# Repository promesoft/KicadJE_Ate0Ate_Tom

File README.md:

# KicadJE_Ate0Ate_Tom
Based on Hexinverter

First Drum module

# Purpose
1 - Match Hexinverter sch with Resynthesis panel

# Status - delivered
## Initial 
| Stage  | Detail | Status |
| ------------- | ------------- | ------------- |
| create material  | sch/pcb | OK  |
| | gerber | OK |
| production  |   | ok |
|  | produced | ok |
|  | delivered | ok |

## Preliminary validation
| Test  | Detail | Status |
| ------------- | ------------- | ------------- |
| Initial Inspection | |  |
| Initial Technical Test |  | |
| Initial Product Test |  | |

## Secondary validation
| Test  | Detail | Status |
| ------------- | ------------- |------------- |
| Product Test |  | |
| Product Test |  |  |
| Quality | | |
| Quality |  |  |
| Long Term Product Test |  |  |
| Power Draw |  | 

## Errata
### Errata - Ate0Ate Tom

## Issues and Notes
### Tom
1 -

2 - 

# Pictures

# Inspiration from 
https://www.resynthesis.shop/epages/zuunneamm4zd.sf/en_GB/?ObjectPath=/Shops/zuunneamm4zd/Products/REEU-HEX-808-TM1

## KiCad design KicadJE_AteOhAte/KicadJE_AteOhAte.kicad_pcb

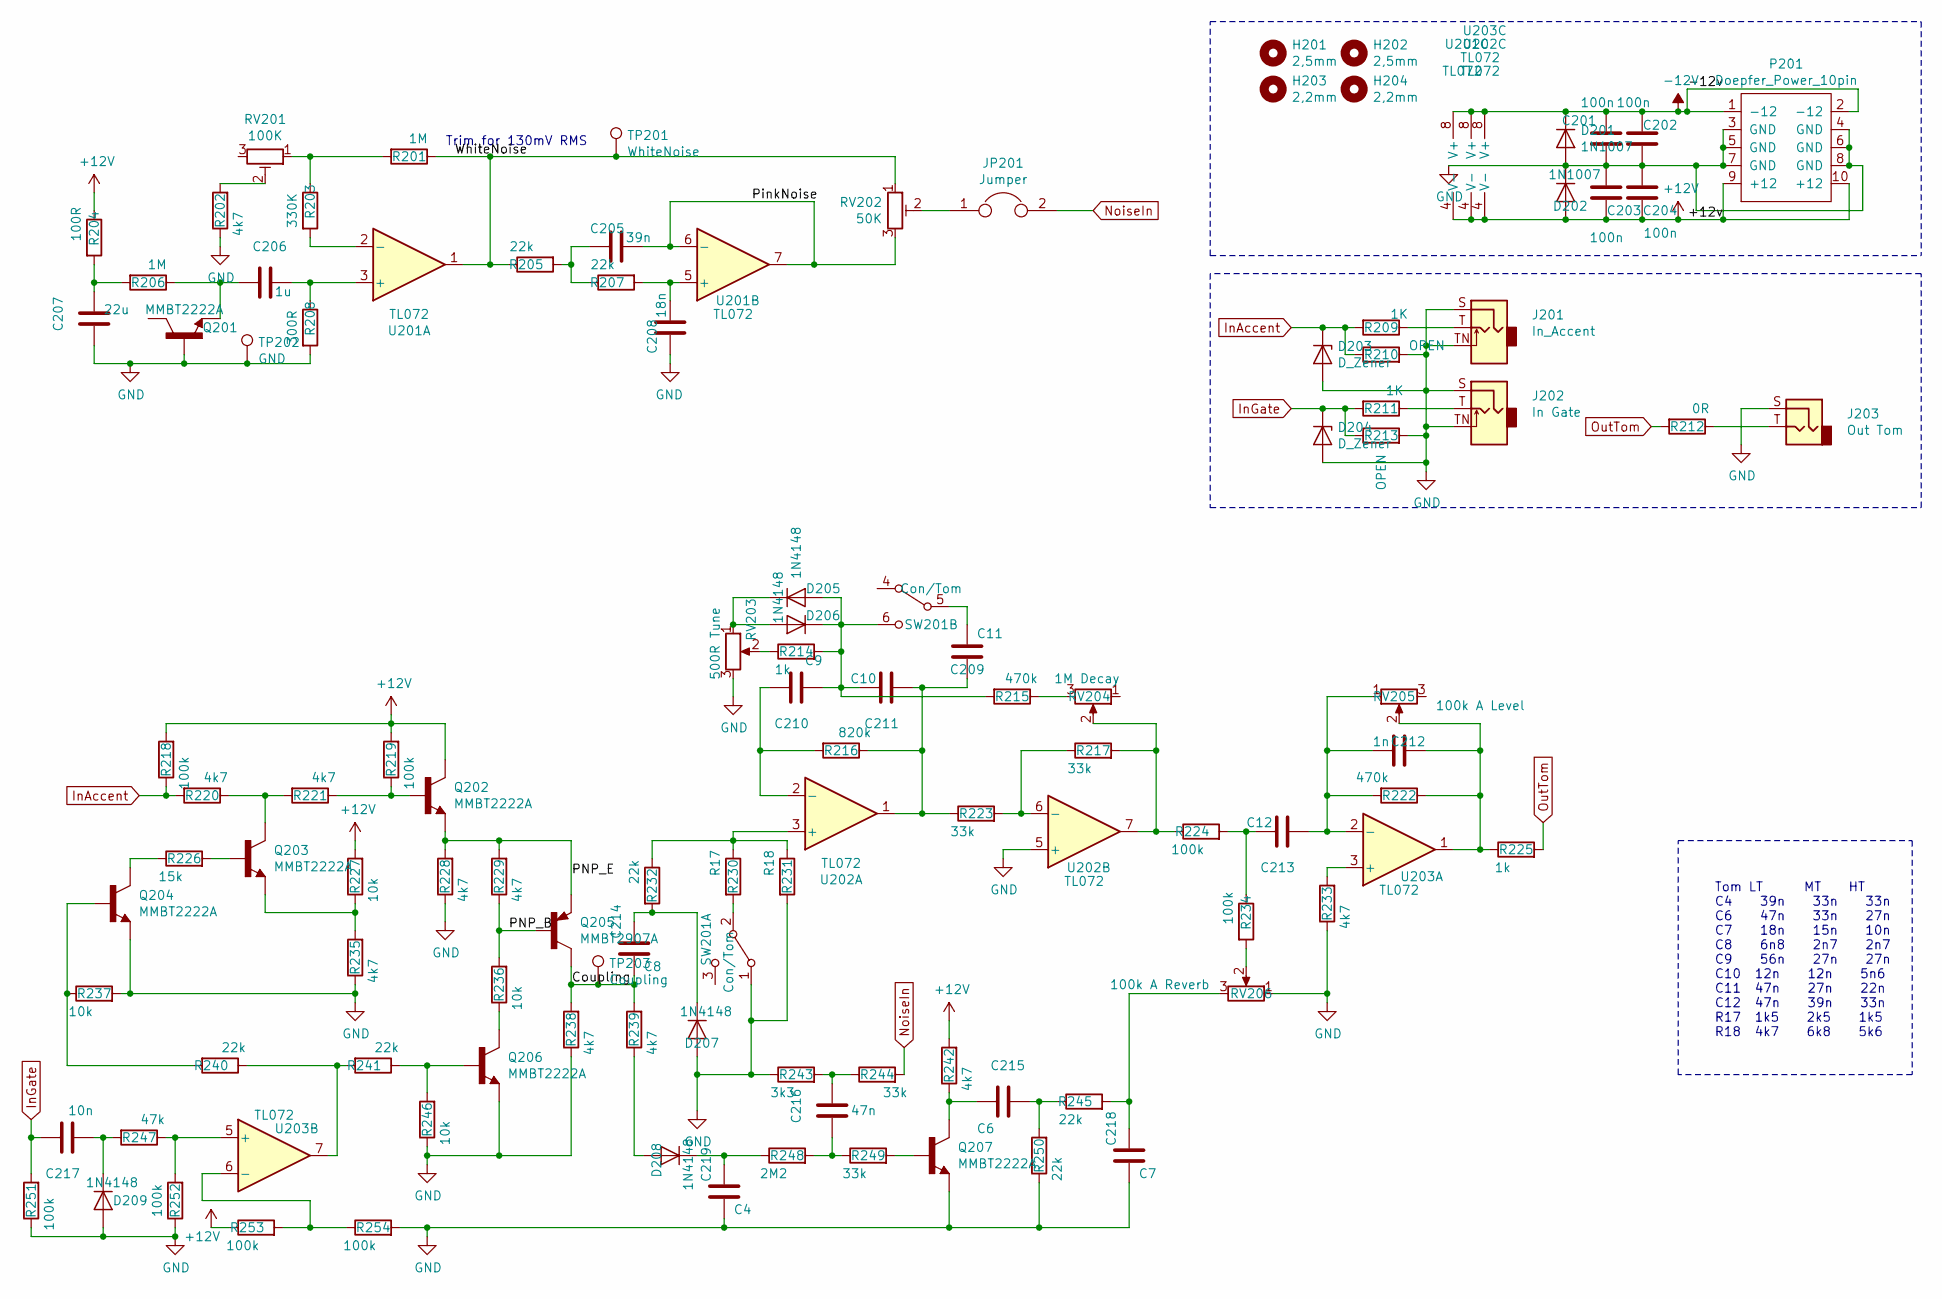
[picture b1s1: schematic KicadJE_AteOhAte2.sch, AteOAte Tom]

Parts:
C201, C202, C203, C204: 100n; C_0805_2012Metric_Pad1.15x1.40mm_HandSolder
C205: 39n; C_0805_2012Metric_Pad1.15x1.40mm_HandSolder
C206: 1u; C_0805_2012Metric_Pad1.15x1.40mm_HandSolder
C207: 22u; C_0805_2012Metric_Pad1.15x1.40mm_HandSolder
C208: 18n; C_0805_2012Metric_Pad1.15x1.40mm_HandSolder
C209: C11; C_0805_2012Metric_Pad1.15x1.40mm_HandSolder
C210: C9; C_0805_2012Metric_Pad1.15x1.40mm_HandSolder
C211: C10; C_0805_2012Metric_Pad1.15x1.40mm_HandSolder
C212: 1n; C_0805_2012Metric_Pad1.15x1.40mm_HandSolder
C213: C12; C_0805_2012Metric_Pad1.15x1.40mm_HandSolder
C214: C8; C_0805_2012Metric_Pad1.15x1.40mm_HandSolder
C215: C6; C_0805_2012Metric_Pad1.15x1.40mm_HandSolder
C216: 47n; C_0805_2012Metric_Pad1.15x1.40mm_HandSolder
C217: 10n; C_0805_2012Metric_Pad1.15x1.40mm_HandSolder
C218: C7; C_0805_2012Metric_Pad1.15x1.40mm_HandSolder
C219: C4; C_0805_2012Metric_Pad1.15x1.40mm_HandSolder
D201, D202: 1N1007; D_SOD-123
D203, D204: D_Zener; D_MiniMELF
D205, D206, D207, D208, D209: 1N4148; D_SOD-123
H201, H202: 2,5mm; MountingHole_2.5mm_Pad_Via
H203, H204: 2,2mm; MountingHole_2.2mm_M2_Pad_Via
J201: In_Accent; Jack_3.5mm_Ledino_KB3SPRS_Horizontal
J202: In Gate; PJ301SM
J203: Out Tom; PJ301SM
JP201: Jumper; PinHeader_1x02_P2.54mm_Vertical
P201: Doepfer_Power_10pin; IDC-Header_2x05_Pitch2.54mm_Straight
Q201, Q202, Q203, Q204, Q206, Q207: MMBT2222A; SOT-23_Handsoldering
Q205: MMBT2907A; SOT-23_Handsoldering
R201, R206: 1M; R_0805_2012Metric_Pad1.15x1.40mm_HandSolder
R202, R220, R221, R228, R229, R233, R235, R238, R239, R242: 4k7; R_0805_2012Metric_Pad1.15x1.40mm_HandSolder
R203: 330K; R_0805_2012Metric_Pad1.15x1.40mm_HandSolder
R204: 100R; R_0805_2012Metric_Pad1.15x1.40mm_HandSolder
R205, R207, R232, R240, R241, R245, R250: 22k; R_0805_2012Metric_Pad1.15x1.40mm_HandSolder
R208: 300R; R_0805_2012Metric_Pad1.15x1.40mm_HandSolder
R209, R211: 1K; R_0805_2012Metric_Pad1.15x1.40mm_HandSolder
R210, R213: OPEN; R_0805_2012Metric_Pad1.15x1.40mm_HandSolder
R212: 0R; R_0805_2012Metric_Pad1.15x1.40mm_HandSolder
R214, R225: 1k; R_0805_2012Metric_Pad1.15x1.40mm_HandSolder
R215, R222: 470k; R_0805_2012Metric_Pad1.15x1.40mm_HandSolder
R216: 820k; R_0805_2012Metric_Pad1.15x1.40mm_HandSolder
R217, R223, R244, R249: 33k; R_0805_2012Metric_Pad1.15x1.40mm_HandSolder
R218, R219, R224, R234, R251, R252, R253, R254: 100k; R_0805_2012Metric_Pad1.15x1.40mm_HandSolder
R226: 15k; R_0805_2012Metric_Pad1.15x1.40mm_HandSolder
R227, R236, R237, R246: 10k; R_0805_2012Metric_Pad1.15x1.40mm_HandSolder
R230: R17; R_0805_2012Metric_Pad1.15x1.40mm_HandSolder
R231: R18; R_0805_2012Metric_Pad1.15x1.40mm_HandSolder
R243: 3k3; R_0805_2012Metric_Pad1.15x1.40mm_HandSolder
R247: 47k; R_0805_2012Metric_Pad1.15x1.40mm_HandSolder
R248: 2M2; R_0805_2012Metric_Pad1.15x1.40mm_HandSolder
RV201: 100K; Potentiometer_Bourns_3296W_Vertical
RV202: 50K; Potentiometer_Bourns_3296W_Vertical
RV203: 500R Tune; Potentiometer_Piher_T-16H_Single_Horizontal
RV204: 1M Decay; Potentiometer_Piher_T-16H_Single_Horizontal
RV205: 100k A Level; Potentiometer_Piher_T-16H_Single_Horizontal
RV206: 100k A Reverb; Potentiometer_Piher_T-16H_Single_Horizontal
SW201: Con/Tom; SPDTx2
TP201: WhiteNoise; TestPoint_Pad_1.5x1.5mm
TP202: GND; TestPoint_THTPad_2.0x2.0mm_Drill1.0mm
TP203: Coupling; TestPoint_Pad_1.5x1.5mm
U201, U202, U203: TL072; AJ_SO-8_5.3x6.2mm_P1.27mm

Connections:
+12V: C203.1, C204.1, D202.2 (A), P201.9 (+12), P201.10 (+12), Q202.3 (C), R204.1, R218.2, R219.2, R227.2, R242.2, R253.1, U201.4 (V-), U202.4 (V-), U203.4 (V-); also elsewhere on the board
-12V: C201.2, C202.2, D201.1 (K), P201.1 (-12), P201.2 (-12), U201.8 (V+), U202.8 (V+), U203.8 (V+); also elsewhere on the board
/KicadJE_AteOhAte2/Coupling: C214.2, Q205.3 (C), R238.2, R239.2, TP203.1
/KicadJE_AteOhAte2/PNP_B: Q205.1 (B), R229.1, R236.2
/KicadJE_AteOhAte2/PNP_E: Q202.2 (E), Q205.2 (E), R228.2, R229.2
/KicadJE_AteOhAte2/PinkNoise: C205.1, RV202.3, U201.6 (-), U201.7
/KicadJE_AteOhAte2/WhiteNoise: R201.1, R205.1, RV202.1, TP201.1, U201.1
GND: C201.1, C202.1, C203.2, C204.2, C207.2, C208.2, C218.2, C219.2, D201.2 (A), D202.1 (K), D203.2 (A), D204.2 (A), D207.2 (A), D209.2 (A), J201.S, J201.TN, J202.S, J202.TN, J203.S, P201.3 (GND), P201.4 (GND), P201.5 (GND), P201.6 (GND), P201.7 (GND), P201.8 (GND), Q201.1 (B), Q204.2 (E), Q206.2 (E), Q207.2 (E), R202.1, R208.2, R210.2, R213.2, R228.1, R231.2, R233.1, R235.1, R237.2, R238.1, R243.1, R246.1, R250.1, R251.1, R252.1, R254.2, RV203.3, RV206.1, SW201.1 (A), TP202.1, U202.5 (+); also elsewhere on the board
InAccent: D203.1 (K), R209.2, R210.1, R218.1, R220.2
InGate: C217.1, D204.1 (K), R211.2, R213.1, R251.2
unnamed: C205.2, R205.2, R207.1
unnamed: C206.1, R208.1, U201.3 (+)
unnamed: C206.2, Q201.2 (E), R206.1
unnamed: C207.1, R204.2, R206.2
unnamed: C208.1, R207.2, U201.5 (+)
unnamed: C209.1, SW201.5 (B)
unnamed: C209.2, C211.2, R216.1, R223.1, U202.1
unnamed: C210.1, R216.2, U202.2 (-)
unnamed: C210.2, C211.1, D205.2 (A), D206.1 (K), R214.2, R215.2, SW201.6 (C)
unnamed: C212.1, C213.2, R222.2, RV205.1, U203.2 (-)
unnamed: C212.2, R222.1, R225.1, RV205.2, U203.1
unnamed: C213.1, R224.2, R234.1
unnamed: C214.1, D207.1 (K), R232.2
unnamed: C215.1, R245.1, R250.2
unnamed: C215.2, Q207.3 (C), R242.1
unnamed: C216.1, R243.2, R244.1
unnamed: C216.2, R248.2, R249.1
unnamed: C217.2, D209.1 (K), R247.2
unnamed: C218.1, R245.2, RV206.3
unnamed: C219.1, D208.1 (K), R248.1
unnamed: D205.1 (K), D206.2 (A), RV203.1
unnamed: D208.2 (A), R239.1
unnamed: J201.T, R209.1
unnamed: J202.T, R211.1
unnamed: J203.T, R212.1
unnamed: JP201.1, RV202.2
unnamed: Q202.1 (B), R219.1, R221.1
unnamed: Q203.1 (B), R226.2
unnamed: Q203.2 (E), R227.1, R235.2
unnamed: Q203.3 (C), R220.1, R221.2
unnamed: Q204.1 (B), R237.1, R240.2
unnamed: Q204.3 (C), R226.1
unnamed: Q206.1 (B), R241.1, R246.2
unnamed: Q206.3 (C), R236.1
unnamed: Q207.1 (B), R249.2
unnamed: R201.2, R203.1, RV201.1
unnamed: R202.2, RV201.2
unnamed: R203.2, U201.2 (-)
unnamed: R214.1, RV203.2
unnamed: R215.1, RV204.3
unnamed: R217.1, R223.2, U202.6 (-)
unnamed: R217.2, R224.1, RV204.2, U202.7
unnamed: R230.1, R231.1, R232.1, U202.3 (+)
unnamed: R230.2, SW201.2 (B)
unnamed: R233.2, U203.3 (+)
unnamed: R234.2, RV206.2
unnamed: R240.1, R241.2, U203.7
unnamed: R247.1, R252.2, U203.5 (+)
unnamed: R253.2, R254.1, U203.6 (-)
NoiseIn: JP201.2, R244.2
OutTom: R212.2, R225.2

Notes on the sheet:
Tom LT MT HT C4 39n 33n 33n C6 47n 33n 27n C7 18n 15n 10n C8 6n8 2n7 2n7 C9 56n 27n 27n C10 12n 12n 5n6 C11 47n 27n 22n C12 47n 39n 33n R17 1k5 2k5 1k5 R18 4k7 6k8 5k6
Trim for 130mV RMS

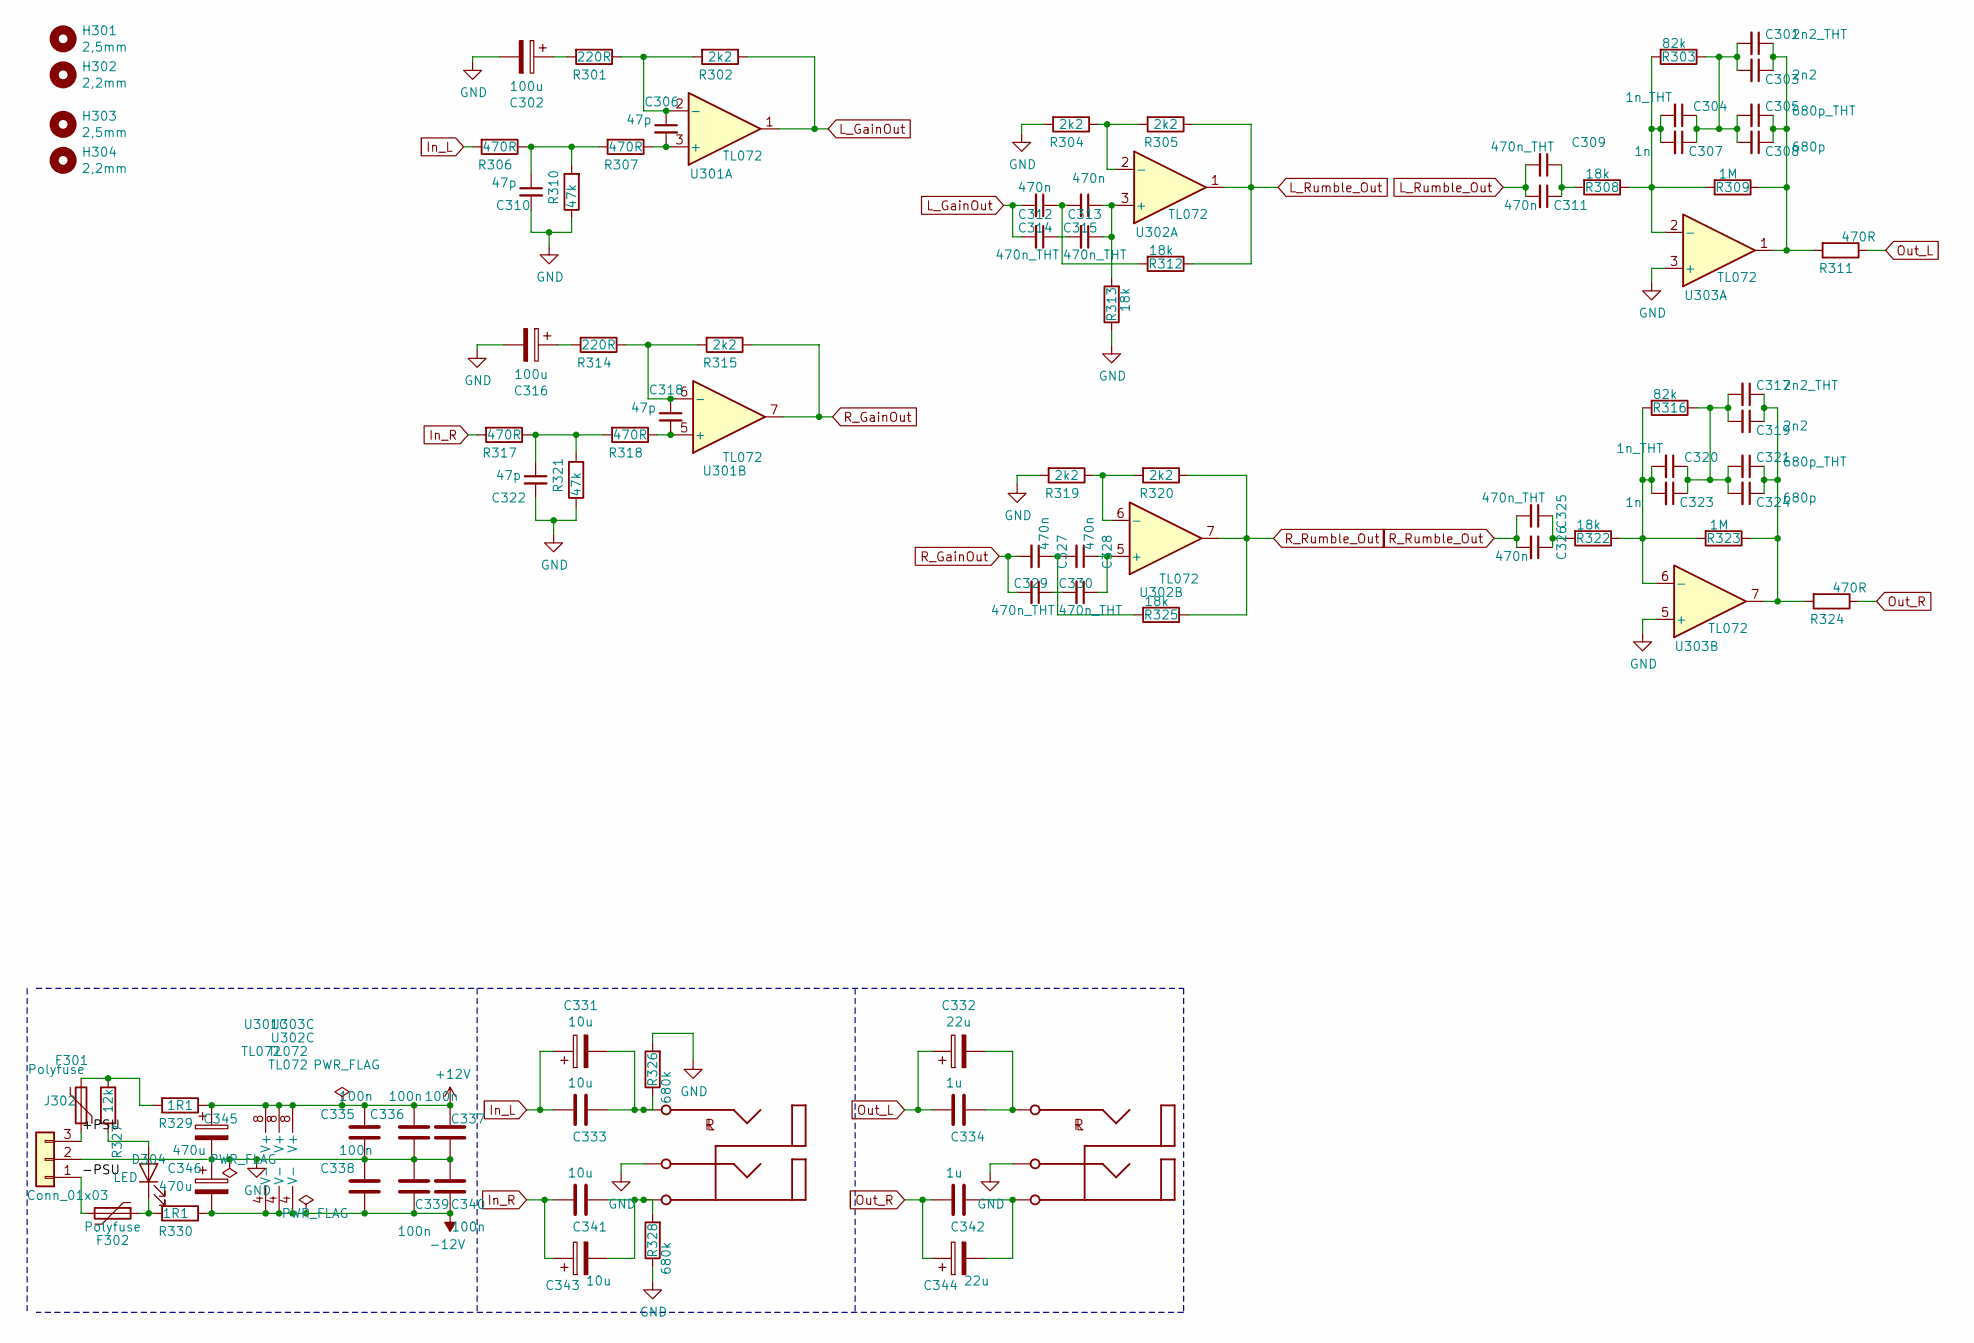
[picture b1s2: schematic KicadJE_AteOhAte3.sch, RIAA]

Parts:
C301, C317: 2n2_THT; C_Rect_L7.2mm_W5.5mm_P5.00mm_FKS2_FKP2_MKS2_MKP2
C302, C316: 100u; CP_Elec_8x6.5
C303, C319: 2n2; C_0805_2012Metric_Pad1.15x1.40mm_HandSolder
C304, C320: 1n_THT; C_Rect_L7.2mm_W5.5mm_P5.00mm_FKS2_FKP2_MKS2_MKP2
C305, C321: 680p_THT; C_Rect_L7.2mm_W5.5mm_P5.00mm_FKS2_FKP2_MKS2_MKP2
C306, C310, C318, C322: 47p; C_0805_2012Metric_Pad1.15x1.40mm_HandSolder
C307, C323: 1n; C_0805_2012Metric_Pad1.15x1.40mm_HandSolder
C308, C324: 680p; C_0805_2012Metric_Pad1.15x1.40mm_HandSolder
C309, C314, C315, C325, C329, C330: 470n_THT; C_Rect_L7.2mm_W5.5mm_P5.00mm_FKS2_FKP2_MKS2_MKP2
C311, C326: 470n; C_1206_3216Metric_Pad1.42x1.75mm_HandSolder
C312, C313, C327, C328: 470n; C_0805_2012Metric_Pad1.15x1.40mm_HandSolder
C331, C343: 10u; CP_Radial_D8.0mm_P3.50mm
C332, C344: 22u; CP_Radial_D8.0mm_P3.50mm
C333, C341: 10u; C_0805_2012Metric_Pad1.15x1.40mm_HandSolder
C334, C342: 1u; C_0805_2012Metric_Pad1.15x1.40mm_HandSolder
C335, C336, C337, C338, C339, C340: 100n; C_0805_2012Metric_Pad1.15x1.40mm_HandSolder
C345, C346: 470u; CP_Radial_D13.0mm_P5.00mm
D304: LED; LED_D3.0mm
F301, F302: Polyfuse; Fuse_1206_3216Metric
H301, H303: 2,5mm; MountingHole_2.5mm_Pad_Via
H302, H304: 2,2mm; MountingHole_2.2mm_M2_Pad_Via
J301: PJRAS2X2S01AUX; PJRAS2X2S01AUX_RCA
J302: Conn_01x03; TerminalBlock_bornier-3_P5.08mm
R301, R314: 220R; R_0805_2012Metric_Pad1.15x1.40mm_HandSolder
R302, R304, R305, R315, R319, R320: 2k2; R_0805_2012Metric_Pad1.15x1.40mm_HandSolder
R303, R316: 82k; R_0805_2012Metric_Pad1.15x1.40mm_HandSolder
R306, R307, R311, R317, R318, R324: 470R; R_0805_2012Metric_Pad1.15x1.40mm_HandSolder
R308, R312, R313, R322, R325: 18k; R_0805_2012Metric_Pad1.15x1.40mm_HandSolder
R309, R323: 1M; R_0805_2012Metric_Pad1.15x1.40mm_HandSolder
R310, R321: 47k; R_0805_2012Metric_Pad1.15x1.40mm_HandSolder
R326, R328: 680k; R_0805_2012Metric_Pad1.15x1.40mm_HandSolder
R327: 12k; R_0805_2012Metric_Pad1.15x1.40mm_HandSolder
R329, R330: 1R1; R_0805_2012Metric_Pad1.15x1.40mm_HandSolder
U301, U302, U303: TL072; AJ_SO-8_5.3x6.2mm_P1.27mm

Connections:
+12V: C335.2, C336.2, C337.2, C345.1, R329.1, U301.8 (V+), U302.8 (V+), U303.8 (V+); also elsewhere on the board
-12V: C338.1, C339.1, C340.1, C346.2, R330.1, U301.4 (V-), U302.4 (V-), U303.4 (V-); also elsewhere on the board
/KicadJE_AteOhAte3/+PSU: F301.1, J302.3
/KicadJE_AteOhAte3/-PSU: F302.2, J302.1
GND: C302.2, C310.2, C316.2, C322.2, C335.1, C336.1, C337.1, C338.2, C339.2, C340.2, C345.2, C346.1, J301.1T1, J301.2T1, R304.2, R310.1, R313.1, R319.2, R321.1, R326.2, R328.1, U303.3 (+), U303.5 (+); also elsewhere on the board
In_L: C331.1, C333.2, R306.2
In_R: C341.2, C343.1, R317.2
L_GainOut: C312.2, C314.2, R302.1, U301.1
L_Rumble_Out: C309.2, C311.2, R305.1, R312.1, U302.1
unnamed: C301.1, C303.1, C305.1, C308.1, R309.1, R311.2, U303.1
unnamed: C301.2, C303.2, C304.1, C305.2, C307.1, C308.2, R303.1
unnamed: C302.1, R301.2
unnamed: C304.2, C307.2, R303.2, R308.1, R309.2, U303.2 (-)
unnamed: C306.1, R301.1, R302.2, U301.2 (-)
unnamed: C306.2, R307.1, U301.3 (+)
unnamed: C309.1, C311.1, R308.2
unnamed: C310.1, R306.1, R307.2, R310.2
unnamed: C313.1, C315.1, R313.2, U302.3 (+)
unnamed: C316.1, R314.2
unnamed: C317.1, C319.1, C321.1, C324.1, R323.1, R324.2, U303.7
unnamed: C317.2, C319.2, C320.1, C321.2, C323.1, C324.2, R316.1
unnamed: C318.1, R314.1, R315.2, U301.6 (-)
unnamed: C318.2, R318.1, U301.5 (+)
unnamed: C320.2, C323.2, R316.2, R322.1, R323.2, U303.6 (-)
unnamed: C322.1, R317.1, R318.2, R321.2
unnamed: C325.1, C326.1, R322.2
unnamed: C328.1, C330.1, U302.5 (+)
unnamed: C331.2, C333.1, J301.2T2, R326.1
unnamed: C332.2, C334.1, J301.1T2
unnamed: C341.1, C343.2, J301.2S, R328.2
unnamed: C342.1, C344.2, J301.1S
unnamed: D304.1 (K), F302.1, R330.2
unnamed: D304.2 (A), R327.2
unnamed: F301.2, R327.1, R329.2
unnamed: R304.1, R305.2, U302.2 (-)
unnamed: R319.1, R320.2, U302.6 (-)
Out_L: C332.1, C334.2, R311.1
Out_R: C342.2, C344.1, R324.1
R_GainOut: C327.2, C329.2, R315.1, U301.7
R_Rumble_Out: C325.2, C326.2, R320.1, R325.1, U302.7

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
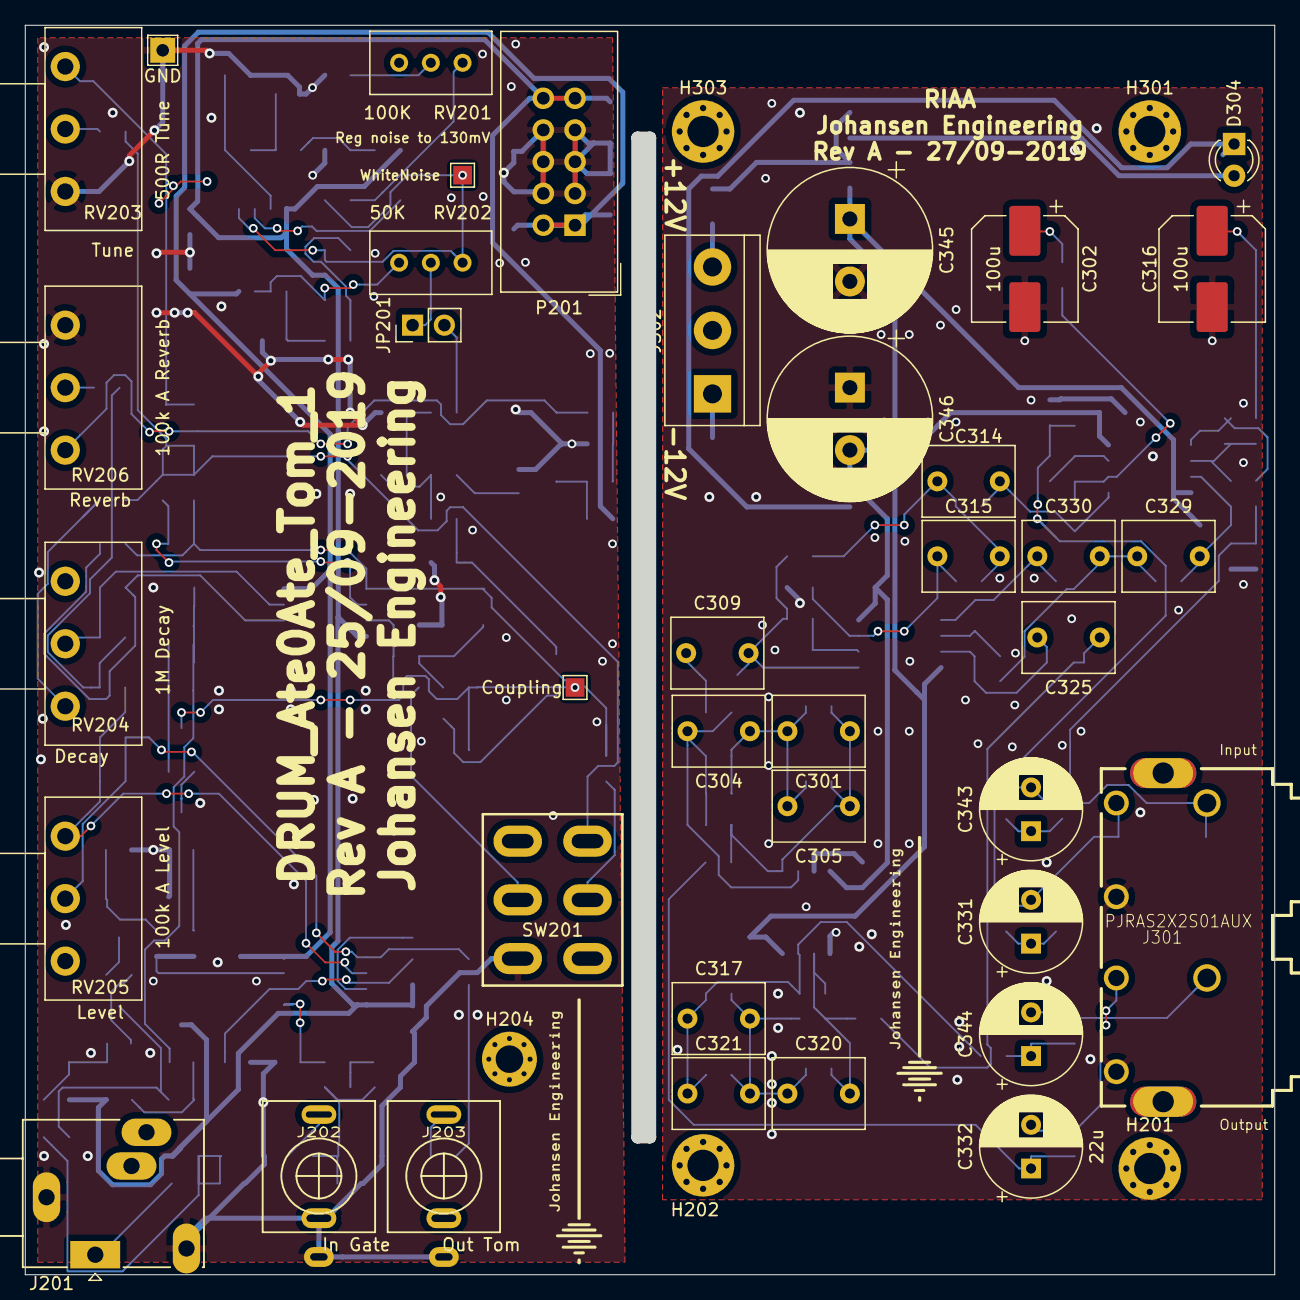
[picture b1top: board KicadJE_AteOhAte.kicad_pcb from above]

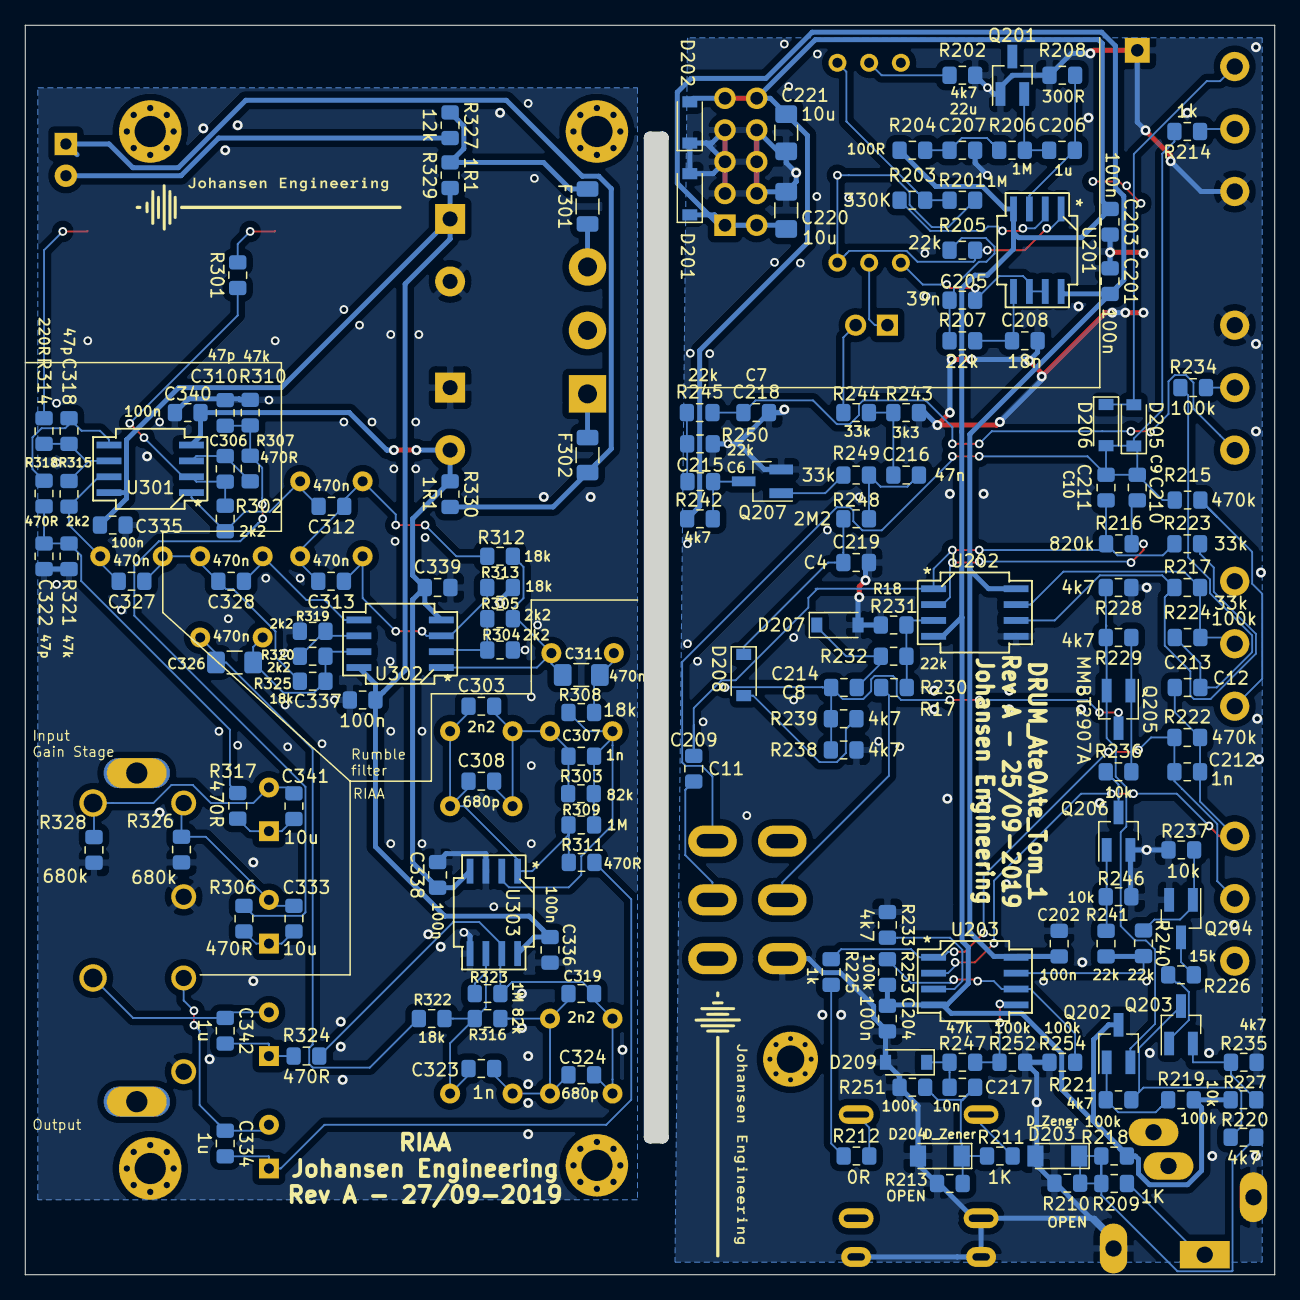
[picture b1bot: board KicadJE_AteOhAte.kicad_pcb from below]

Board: 2 copper layers, 100.0 x 100.0 mm, 198 parts (155 on the bottom side), 100 nets.

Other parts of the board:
C220, C221: 10u; C_1206_3216Metric_Pad1.42x1.75mm_HandSolder

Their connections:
+12V: C221.1; also elsewhere on the board
-12V: C220.2; also elsewhere on the board
GND: C220.1, C221.2; also elsewhere on the board

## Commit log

2019-09-22 Sch initiated
2019-09-22 Sch initiating
2019-09-22 PCB init shape
2019-09-22 ACC and Trig input done sch
2019-09-23 misc
2019-09-23 2nd stage Tom sch initiated
2019-09-23 Initial SCH for the Tom
2019-09-23 LT HT MT vals
2019-09-23 PCB footprint upd
2019-09-23 Noise added
2019-09-23 2907 footprint and more
2019-09-23 Test points for adj
2019-09-25 PCB and Testpoint to coupling
2019-09-25 PCB before copper fill
2019-09-25 RIAA SCH started
2019-09-25 RCA on RIAA
2019-09-26 RIAA Basic Circuit
2019-09-26 SCH Annotate
2019-09-26 sch RIAA
2019-09-26 RIAA RCA
2019-09-26 Capacirtor footprints
2019-09-26 PWR RIAA
2019-09-26 RIAA
2019-09-26 Fused RIAA SCH
2019-09-26 RIAA Basic THT placed
2019-09-26 RIAA decoupling
2019-09-26 SCH Error in RIAA fixed (link C313 327 area)
2019-09-26 90% component placement RIAA
2019-09-26 RIAA Placed and initial route
2019-09-26 Routing and GND on RIAA
2019-09-28 Labels RIAA
2019-09-28 Labels complete RIAA
2019-09-28 Ate0Ate Tom Labels
2019-09-28 Label tweaks
2019-09-28 Label upd and Added 2x caps to pwr
2019-09-28 DRC Check
2019-09-28 Gerber
2019-09-28 Update fp-info-cache
2019-10-02 prep for rev B without RIAA
2019-10-04 RevB
2019-10-04 New tom ext noise
2019-10-04 2nd tom
2019-10-04 Main components placed
2019-10-04 Input placement
2019-10-04 routed and filled
2019-10-04 RevB initial Gerber - before labels
2019-10-04 Finish label and gerber
2019-10-04 remove excess components
2019-10-04 RevB upd
2021-01-29 Update README.md
    Top1
